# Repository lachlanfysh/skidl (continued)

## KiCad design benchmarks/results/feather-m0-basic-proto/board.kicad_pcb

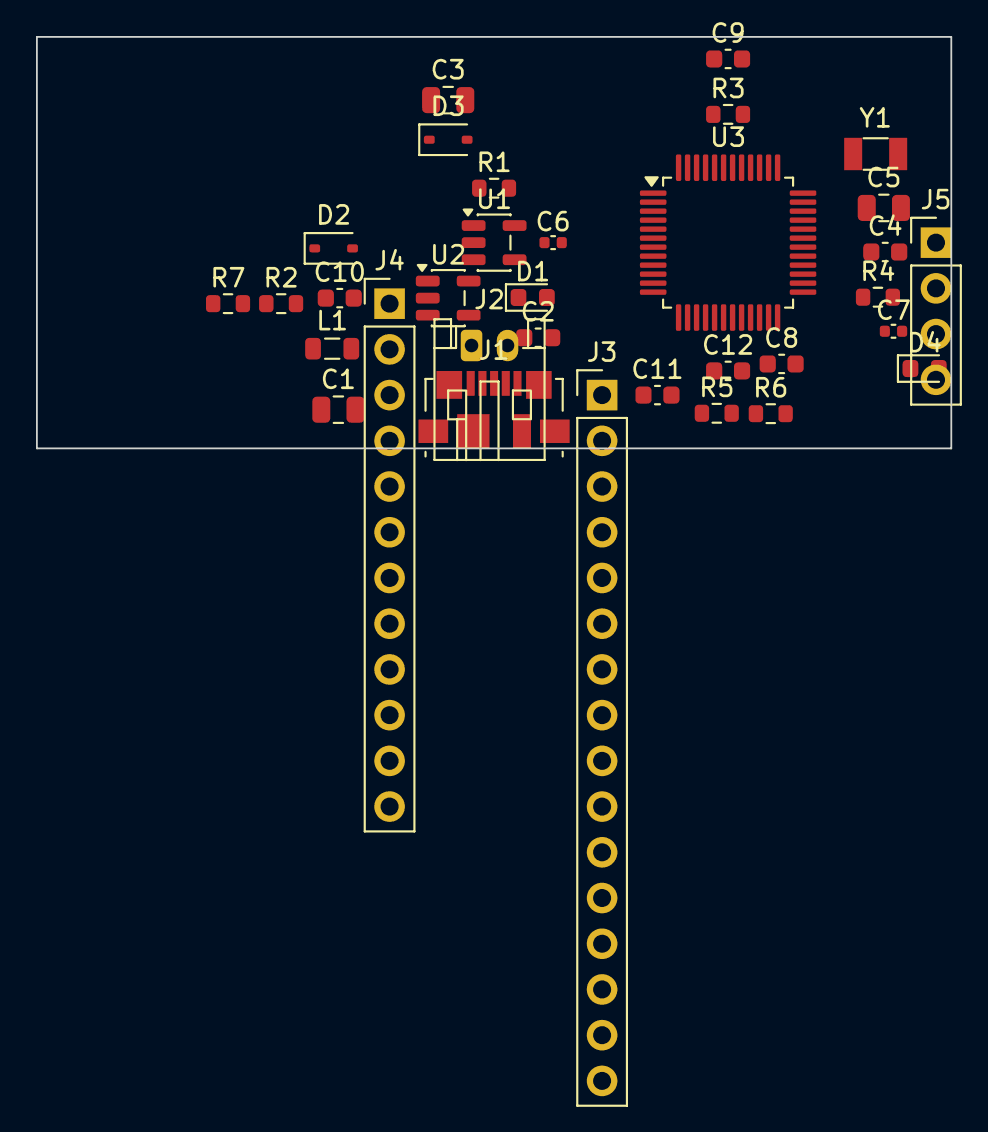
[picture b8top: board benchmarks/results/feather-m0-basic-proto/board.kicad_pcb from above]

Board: 2 copper layers, 50.8 x 22.9 mm, 33 parts (0 on the bottom side), 39 nets, no tracks yet.

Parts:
C1, C3, C5: 10uF; C_0805_2012Metric
C2, C4, C8, C10, C11, C12: 100nF; C_0603_1608Metric
C6, C7: 12pF; C_0402_1005Metric
C9: 1uF; C_0603_1608Metric
D1: Orange; LED_0603_1608Metric
D2, D3: MBR0520; D_SOD-323
D4: Red; LED_0603_1608Metric
J1: USB_Micro_B; USB_Micro-B_Molex_47346-0001
J2: JST_PH_2; JST_PH_S2B-PH-K_1x02_P2.00mm_Horizontal
J3: Feather_Left; PinHeader_1x16_P2.54mm_Vertical
J4: Feather_Right; PinHeader_1x12_P2.54mm_Vertical
J5: SWD; PinHeader_1x04_P2.54mm_Vertical
L1: 600R@100MHz; L_0805_2012Metric
R1: 2K; R_0603_1608Metric
R2, R7: 1K; R_0603_1608Metric
R3, R4: 100K; R_0603_1608Metric
R5: 10K; R_0603_1608Metric
R6: SW_RST; R_0603_1608Metric
U1: MCP73831; SOT-23-5
U2: AP2112K-3.3; SOT-23-5
U3: ATSAMD21G18A; TQFP-48_7x7mm_P0.5mm
Y1: 32.768kHz; Crystal_SMD_3215-2Pin_3.2x1.5mm

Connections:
+3V3: C4.1, C5.1, C10.1, C11.1, C12.1, J3.2, J3.3, J5.1, R5.1, U2.5, U3.6, U3.17, U3.36, U3.44
BAT_DIV: R3.2, R4.1, U3.12
GND: C1.2, C2.2, C3.2, C4.2, C5.2, C6.2, C7.2, C8.2, C9.2, C10.2, C11.2, C12.2, D4.1, J1.5, J1.6, J2.2, J3.4, J5.4, R1.2, R4.2, R6.2, U1.2, U2.2, U3.5, U3.18, U3.35, U3.42
HL_0: J3.5, U3.3
HL_1: J3.6, U3.4
HL_2: J3.7, U3.7
HL_3: J3.8, U3.8
HL_4: J3.9, U3.9
HL_5: J3.10, U3.10
HL_6: J3.11, U3.11
HR_0: J4.4, R7.1, U3.26
HR_1: J4.5, U3.28
HR_2: J4.6, U3.25
HR_3: J4.7, U3.27
HR_4: J4.8, U3.29
HR_5: J4.9, U3.24
HR_6: J4.10, U3.23
HR_7: J3.15, U3.15
HR_8: J3.16, U3.16
MISO: J3.14, U3.21
MOSI: J3.13, U3.19
unnamed: R1.1, U1.5
unnamed: D1.2, R2.2
unnamed: D1.1, U1.1
unnamed: D4.2, R7.2
SCK: J3.12, U3.20
SCL: J4.12, U3.32
SDA: J4.11, U3.31
SWCLK: J5.3, U3.45
SWDIO: J5.2, U3.46
USB_DM: J1.2, U3.33
USB_DP: J1.3, U3.34
VBAT: D3.2, J2.1, J4.1, R3.1, U1.3
VBUS: C1.1, C2.1, D2.2, J1.1, J4.3, L1.1, L1.2, R2.1, U1.4
VCC: C3.1, D2.1, D3.1, U2.1, U2.3
VDDCORE: C9.1, U3.43
XIN: C6.1, U3.1, Y1.1
XOUT: C7.1, U3.2, Y1.2
~RESET: C8.1, J3.1, R5.2, R6.1, U3.40

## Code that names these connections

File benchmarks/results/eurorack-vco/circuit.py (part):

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c_tl_n[1] += gnd; c_tl_n[2] += n12

# Unit A: CV buffer — unity gain non-inverting
# + (pin 3) = CV_IN_NODE; - (pin 2) = CV_BUFFERED (feedback); out (pin 1) = CV_BUFFERED
cv_in  = Net("CV_IN_NODE")
cv_buf = Net("CV_BUFFERED")
tl[3] += cv_in   # Unit A non-inv
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r_cv_sum[2] += cv_sum

# Unit B: PW inverting summer
# + (pin 5) = GND; - (pin 6) = PW_NODE; out (pin 7) = PW_CV
pw_node = Net("PW_NODE")
tl[5] += gnd
tl[6] += pw_node
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
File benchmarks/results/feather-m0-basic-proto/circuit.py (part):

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    vddcore += c_core[1]; gnd += c_core[2]

    # USB D+/D- → PA24/PA25
    usb_dp += u["PA24"]
    usb_dm += u["PA25"]

    # Reset
    mcu_reset += u["~{RESET}"]
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    a5 += u["PB02"]

    # Battery divider on PA07
    bat_div += u["PA07"]

    # Digital header
    d5  += u["PA15"]
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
